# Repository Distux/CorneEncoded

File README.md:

# Corne Encoded
A spinoff (pun intended) of Corne Cherry v2.1. The Corne Cherry 2.1 is a reversible hotswap ortholinear split keyboard pcb.
It has the following changes:
- Added rotary encoder support
- Battery switch (MSK12C02) and terminals
- Silkscreen changes
- Change reset to SKRTLAE010 (sideways button)
- Assembly changes (see build guide)

Projects referenced: Klor, Ferris Sweep, Corne Cherry v2.1
## Issues
- designed for fun, not for production
  
## Production
JLCPCB is recommended, if you produce the gerbers from this [project link](https://oshwlab.com/dungeonstag/corne-encoded) you can save 8$ off your order. The Kicad files are of an older version and will not be updated.

## Image of v1 of pcb

## The Original Corne keyboard

The Corne keyboard is a split keyboard with 3x6 column staggered keys
and 3 thumb keys, based on [Helix](https://github.com/MakotoKurauchi/helix).
Crkbd stands for Corne Keyboard.

## Future Changes
- Add 5th hole for Nice!View support
- Add cool design to silkscreen or delete it all for minimalism
- Rewire LEDS for MINI-E support
- Add power cutoff for LEDs
- Move/add support for JST proper JST housing.

## Images

## Photos

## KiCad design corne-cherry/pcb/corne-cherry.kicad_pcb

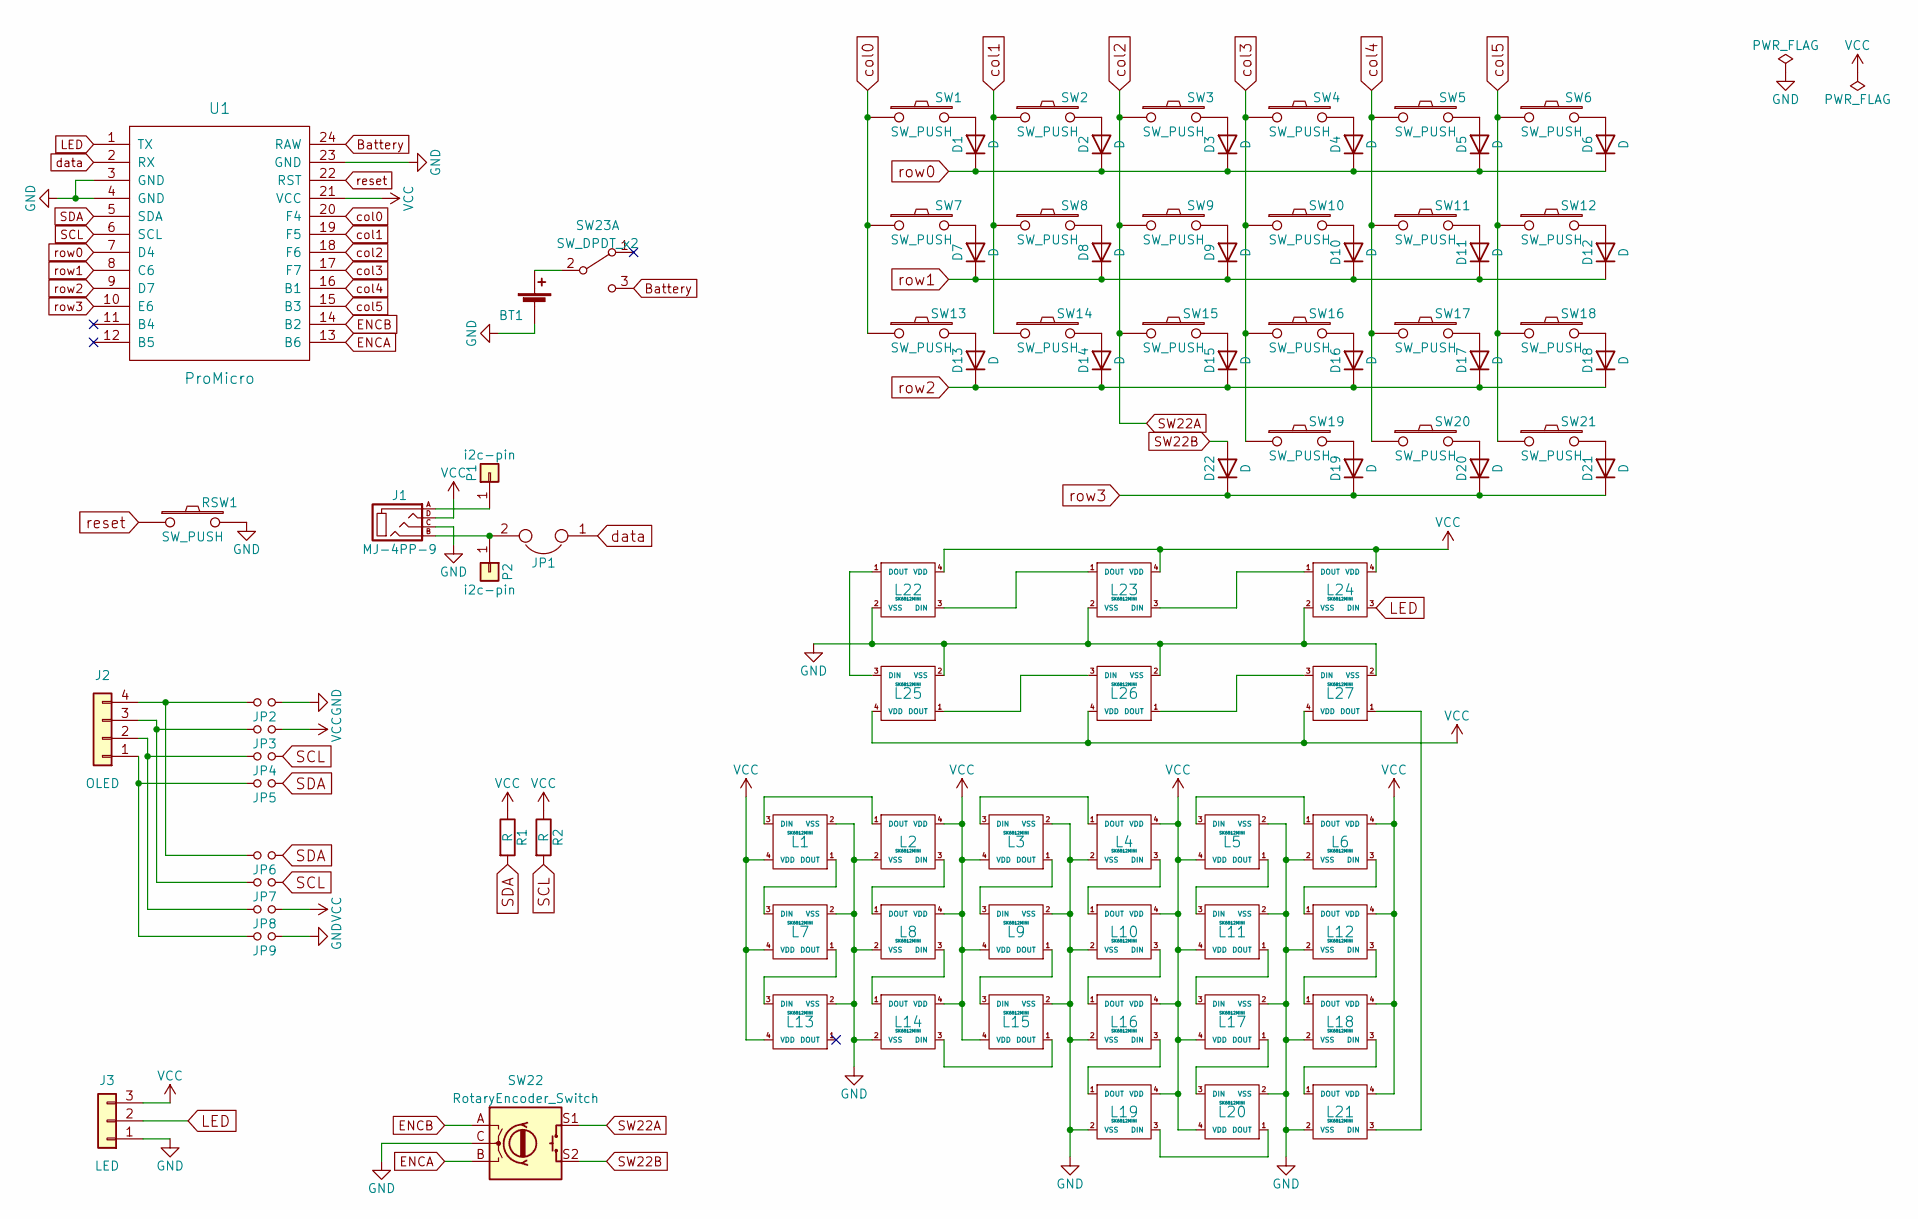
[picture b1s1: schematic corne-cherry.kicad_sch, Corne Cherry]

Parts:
BT1: Battery_Cell; custombatteryconnector_small
D1, D2, D3, D4, D5, D6, D7, D8, D9, D10, D11, D12, D13, D14, D15, D16, D17, D18, D19, D20, D21: D; D3_TH_SMD
D22: D; D3_SMD
J1: MJ-4PP-9
J2: OLED
J3: LED; StripLED_rev
JP1: JPC2
JP2, JP3, JP4, JP5, JP6, JP7, JP8, JP9: Jumper
L1, L2, L3, L4, L5, L6, L7, L8, L9, L10, L11, L12, L13, L14, L15, L16, L17, L18, L19, L20, L21: SK6812MINI; SK6812MINI_rev
L22, L23, L24, L25, L26, L27: SK6812MINI; SK6812MINI_underglow
P1, P2: i2c-pin; 1pin_conn
R1, R2: R
RSW1: SW_PUSH; SW_Push_1P1T-MP_NO_Horizontal_Alps_SKRTLAE010_both_sides
SW1, SW2, SW3, SW4, SW5, SW6, SW7, SW8, SW9, SW10, SW11, SW12, SW13, SW14, SW15, SW16, SW17, SW18, SW19, SW20: SW_PUSH; MX_ALPS_PG1350_noLed
SW21: SW_PUSH; MX_ALPS_PG1350_noLed_1.75u
SW22: RotaryEncoder_Switch; RotaryEncoder_Alps_EC11E-Switch_Vertical_H20mm-keebio_modif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
SW23: SW_DPDT_x2; MSK12C02_reversible
U1: ProMicro; ProMicro_v2

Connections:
Battery: SW23.3 (C), U1.24 (RAW)
ENCA: SW22.B, U1.13 (B6)
ENCB: SW22.A, U1.14 (B2)
GND: BT1.2 (-), J1.C, J3.1, JP2.1, JP9.1, L1.2 (VSS), L2.2 (VSS), L3.2 (VSS), L4.2 (VSS), L5.2 (VSS), L6.2 (VSS), L7.2 (VSS), L8.2 (VSS), L9.2 (VSS), L10.2 (VSS), L11.2 (VSS), L12.2 (VSS), L13.2 (VSS), L14.2 (VSS), L15.2 (VSS), L16.2 (VSS), L17.2 (VSS), L18.2 (VSS), L19.2 (VSS), L20.2 (VSS), L21.2 (VSS), L22.2 (VSS), L23.2 (VSS), L24.2 (VSS), L25.2 (VSS), L26.2 (VSS), L27.2 (VSS), RSW1.2, SW22.C, U1.3 (GND), U1.4 (GND), U1.23 (GND)
LED: J3.2, L24.3 (DIN), U1.1 (TX)
unnamed: BT1.1 (+), SW23.2 (B)
unnamed: D1.2 (A), SW1.2
unnamed: D2.2 (A), SW2.2
unnamed: D3.2 (A), SW3.2
unnamed: D4.2 (A), SW4.2
unnamed: D5.2 (A), SW5.2
unnamed: D6.2 (A), SW6.2
unnamed: D7.2 (A), SW7.2
unnamed: D8.2 (A), SW8.2
unnamed: D9.2 (A), SW9.2
unnamed: D10.2 (A), SW10.2
unnamed: D11.2 (A), SW11.2
unnamed: D12.2 (A), SW12.2
unnamed: D13.2 (A), SW13.2
unnamed: D14.2 (A), SW14.2
unnamed: D15.2 (A), SW15.2
unnamed: D16.2 (A), SW16.2
unnamed: D17.2 (A), SW17.2
unnamed: D18.2 (A), SW18.2
unnamed: D19.2 (A), SW19.2
unnamed: D20.2 (A), SW20.2
unnamed: D21.2 (A), SW21.2
unnamed: J2.1, JP5.2, JP9.2
unnamed: J2.2, JP4.2, JP8.2
unnamed: J2.3, JP3.2, JP7.2
unnamed: J2.4, JP2.2, JP6.2
unnamed: L1.3 (DIN), L2.1 (DOUT)
unnamed: L1.1 (DOUT), L7.3 (DIN)
unnamed: L2.3 (DIN), L8.1 (DOUT)
unnamed: L3.3 (DIN), L4.1 (DOUT)
unnamed: L3.1 (DOUT), L9.3 (DIN)
unnamed: L5.3 (DIN), L6.1 (DOUT)
unnamed: L10.3 (DIN), L16.1 (DOUT)
unnamed: L4.3 (DIN), L10.1 (DOUT)
unnamed: L5.1 (DOUT), L11.3 (DIN)
unnamed: L11.1 (DOUT), L17.3 (DIN)
unnamed: L12.3 (DIN), L18.1 (DOUT)
unnamed: L6.3 (DIN), L12.1 (DOUT)
unnamed: L7.1 (DOUT), L13.3 (DIN)
unnamed: L14.3 (DIN), L15.1 (DOUT)
unnamed: L8.3 (DIN), L14.1 (DOUT)
unnamed: L9.1 (DOUT), L15.3 (DIN)
unnamed: L16.3 (DIN), L19.1 (DOUT)
unnamed: L17.1 (DOUT), L20.3 (DIN)
unnamed: L18.3 (DIN), L21.1 (DOUT)
unnamed: L19.3 (DIN), L20.1 (DOUT)
unnamed: L21.3 (DIN), L27.1 (DOUT)
unnamed: L22.3 (DIN), L23.1 (DOUT)
unnamed: L22.1 (DOUT), L25.3 (DIN)
unnamed: L23.3 (DIN), L24.1 (DOUT)
unnamed: L25.1 (DOUT), L26.3 (DIN)
unnamed: L26.1 (DOUT), L27.3 (DIN)
unnamed: J1.A, P1.1
unnamed: J1.B, JP1.2, P2.1
SCL: JP4.1, JP7.1, R2.2, U1.6 (SCL)
SDA: JP5.1, JP6.1, R1.2, U1.5 (SDA)
SW22A: SW3.1, SW9.1, SW15.1, SW22.S1, U1.18 (F6)
SW22B: D22.2 (A), SW22.S2
VCC: J1.D, J3.3, JP3.1, JP8.1, L1.4 (VDD), L2.4 (VDD), L3.4 (VDD), L4.4 (VDD), L5.4 (VDD), L6.4 (VDD), L7.4 (VDD), L8.4 (VDD), L9.4 (VDD), L10.4 (VDD), L11.4 (VDD), L12.4 (VDD), L13.4 (VDD), L14.4 (VDD), L15.4 (VDD), L16.4 (VDD), L17.4 (VDD), L18.4 (VDD), L19.4 (VDD), L20.4 (VDD), L21.4 (VDD), L22.4 (VDD), L23.4 (VDD), L24.4 (VDD), L25.4 (VDD), L26.4 (VDD), L27.4 (VDD), R1.1, R2.1, U1.21 (VCC)
col0: SW1.1, SW7.1, SW13.1, U1.20 (F4)
col1: SW2.1, SW8.1, SW14.1, U1.19 (F5)
col3: SW4.1, SW10.1, SW16.1, SW19.1, U1.17 (F7)
col4: SW5.1, SW11.1, SW17.1, SW20.1, U1.16 (B1)
col5: SW6.1, SW12.1, SW18.1, SW21.1, U1.15 (B3)
data: JP1.1, U1.2 (RX)
reset: RSW1.1, U1.22 (RST)
row0: D1.1 (K), D2.1 (K), D3.1 (K), D4.1 (K), D5.1 (K), D6.1 (K), U1.7 (D4)
row1: D7.1 (K), D8.1 (K), D9.1 (K), D10.1 (K), D11.1 (K), D12.1 (K), U1.8 (C6)
row2: D13.1 (K), D14.1 (K), D15.1 (K), D16.1 (K), D17.1 (K), D18.1 (K), U1.9 (D7)
row3: D19.1 (K), D20.1 (K), D21.1 (K), D22.1 (K), U1.10 (E6)

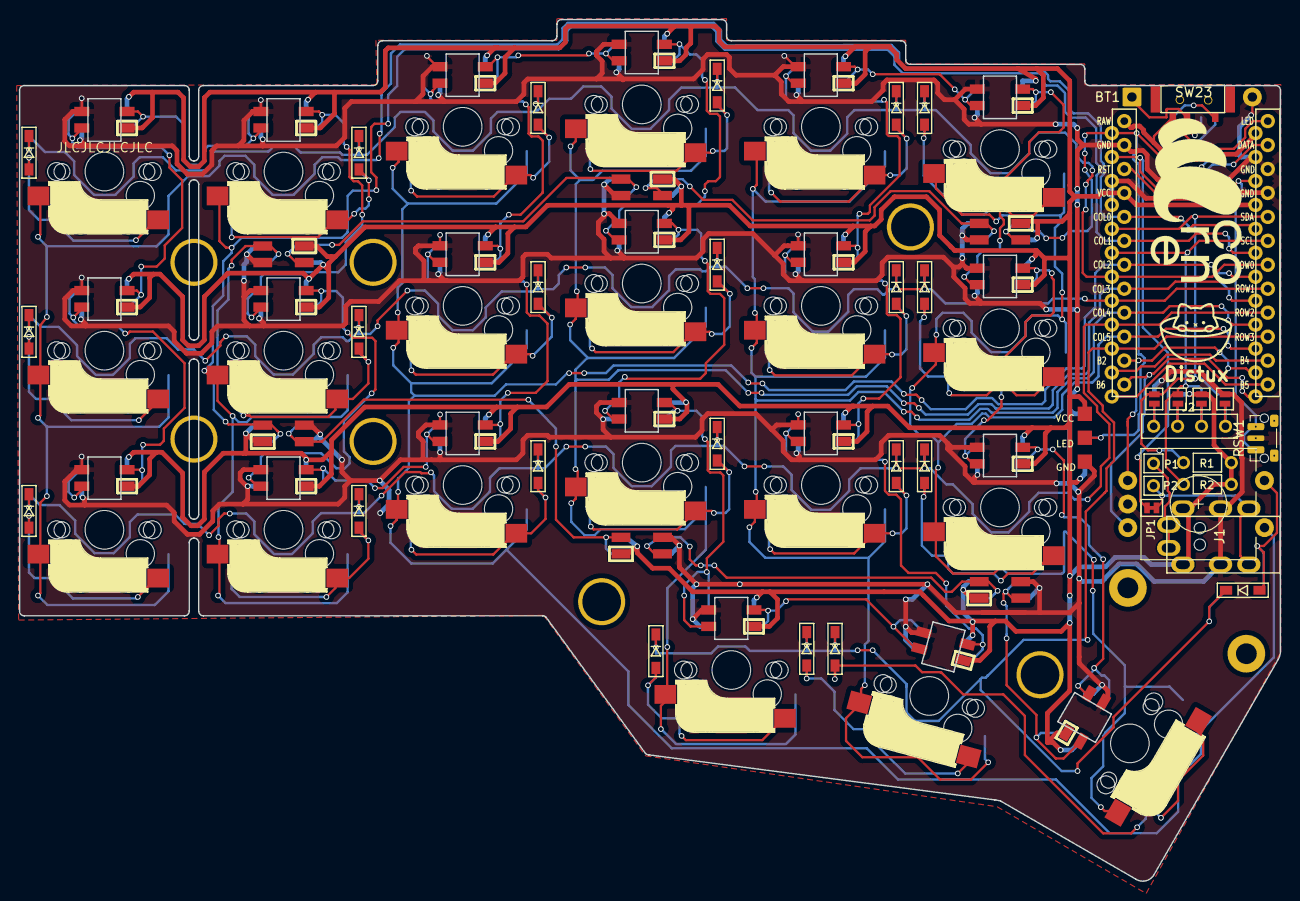
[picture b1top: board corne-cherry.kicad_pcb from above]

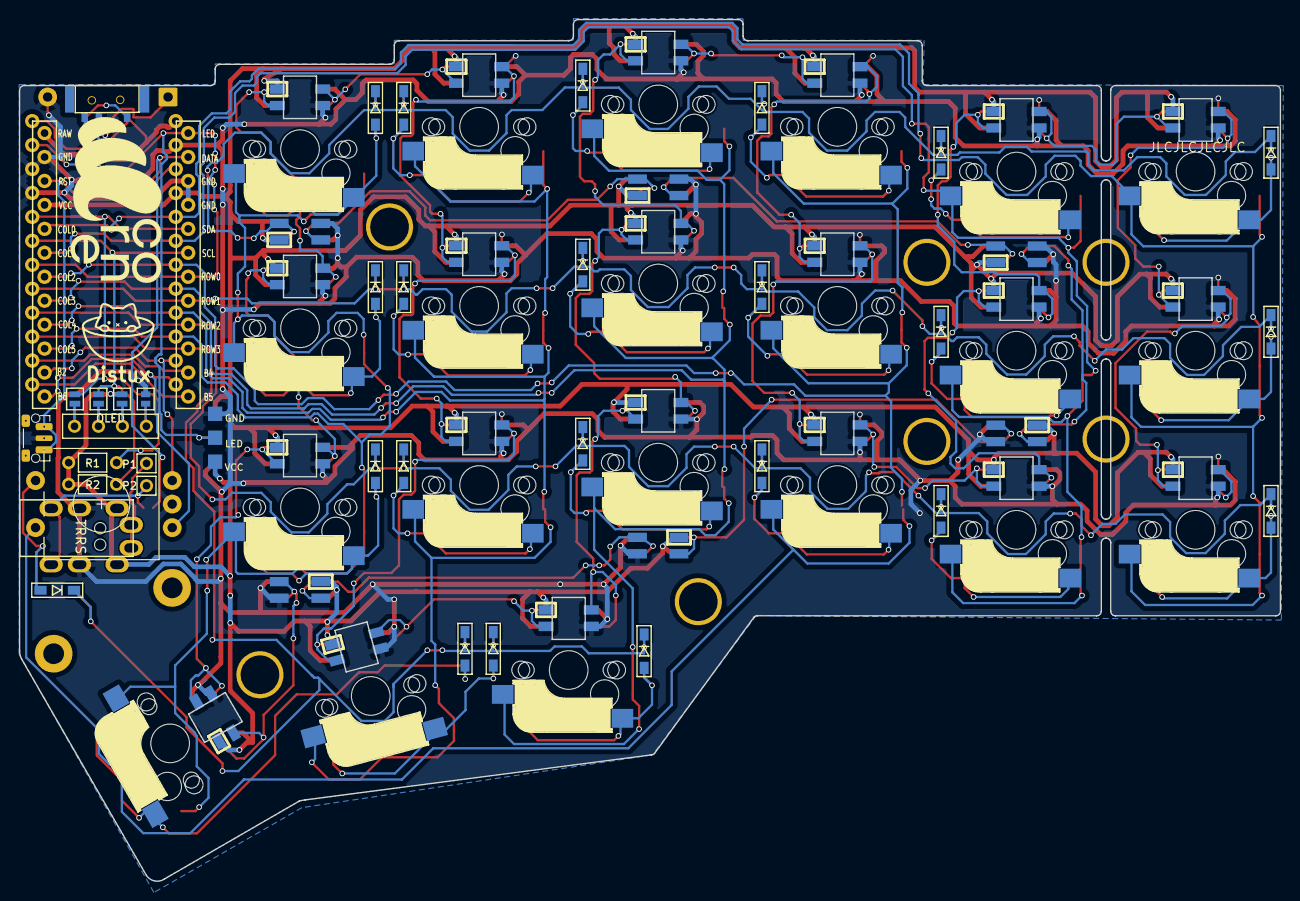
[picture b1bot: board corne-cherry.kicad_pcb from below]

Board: 2 copper layers, 133.8 x 91.4 mm, 91 parts (4 on the bottom side), 75 nets.

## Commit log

2023-06-01 rebase
2023-06-01 Update readme and add PCB
2023-06-01 Update readme and add image folder
2023-06-01 add image
2023-06-01 Update readme for pcb
2023-06-01 Update readme, remove broken link
2023-06-22 Update README.md
    Add future changes, update change list
2023-06-22 Update README.md
    Add issues list
2023-06-22 Add images
2023-06-22 remove unnecessary file
2023-06-22 Update README.md
    Add images to readme
